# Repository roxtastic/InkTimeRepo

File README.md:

# InkWatch — E-Ink Smartwatch based on nRF52840
Tololoi Ilinca-Roxana, 331CB

A compact, low-power smartwatch built around the Nordic Semiconductor nRF52840 SoC and an e-ink display. The PCB measures 32 x 35 mm with rounded corners to fit a wristwatch enclosure. The design prioritizes ultra-low standby current, BLE connectivity, and an always-on e-paper display that retains its image without any power.

---

## Block Diagram

```
+---------------------+
|     LiPo Battery    |
+----------+----------+
           |
           v
+----------+----------+       +-------------------+
|   Charging IC        |       |   USB Type-C       |
|      TP4054          +<------+   (5V input)       |
+----------+----------+       +-------------------+
           |
           v
+----------+----------+
|   LDO 3.3V           |
|      XC6220          |
+----------+----------+
           |
           v
+----------+-------------------------------------------+
|                      nRF52840                        |
|   Cortex-M4F @ 64 MHz, 1MB Flash, 256KB RAM, BLE 5  |
+---+----------+----------+----------+----------------+
    |          |          |          |
    | SPI      | I2C      | GPIO     | USB
    |          |          |          |
    v          v          v          v
+-------+  +-------+  +-------+  +-----------+
| E-Ink |  | RTC   |  | Btns  |  |  USB CDC  |
| Display  | DS3231|  | x2    |  |  DFU      |
| 200x200  +-------+  +-------+  +-----------+
+-------+  +-------+
           | Haptic|
           | DRV   |
           | 2605L |
           +-------+

+-------+
| Flash |   <-- SPI (shared bus with E-Ink)
| W25Q16|
+-------+
```

---

## Bill of Materials (BOM)

| # | Component | Description | Footprint | Qty | JLC Part | Datasheet |
|---|-----------|-------------|-----------|-----|----------|-----------|
| 1 | nRF52840-QIAA | BLE SoC, Cortex-M4F, 1MB Flash | QFN-73 | 1 | [C190794](https://www.lcsc.com/product-detail/C190794.html) | [Link](https://infocenter.nordicsemi.com/pdf/nRF52840_PS_v1.7.pdf) |
| 2 | GDEW0154M10 | 1.54in E-Ink display, 200x200, SPI | FPC 24-pin | 1 | — | [Link](https://www.good-display.com/product/212.html) |
| 3 | DS3231SN | High-accuracy I2C RTC with TCXO | SOIC-16 | 1 | [C9877](https://www.lcsc.com/product-detail/C9877.html) | [Link](https://datasheets.maximintegrated.com/en/ds/DS3231.pdf) |
| 4 | W25Q16JVSSIQ | 16Mbit SPI NOR Flash | SOIC-8 | 1 | [C131025](https://www.lcsc.com/product-detail/C131025.html) | [Link](https://www.winbond.com/resource-files/w25q16jv%20spi%20revh%2004082019%20plus.pdf) |
| 5 | TP4054 | 500mA single-cell LiPo charger | SOT-23-5 | 1 | [C16581](https://www.lcsc.com/product-detail/C16581.html) | [Link](https://www.lcsc.com/datasheet/lcsc_datasheet_1810192335_TPUNITED-TP4054_C16581.pdf) |
| 6 | XC6220A331MR | 300mA LDO 3.3V regulator | SOT-25 | 1 | [C86534](https://www.lcsc.com/product-detail/C86534.html) | [Link](https://product.torexsemi.com/system/files/series/xc6220.pdf) |
| 7 | DRV2605L | Haptic motor driver, I2C | WSON-10 | 1 | [C167749](https://www.lcsc.com/product-detail/C167749.html) | [Link](https://www.ti.com/lit/ds/symlink/drv2605l.pdf) |
| 8 | PRTR5V0U2X | USB ESD protection, dual-rail | SOT-363 | 1 | [C12333](https://www.lcsc.com/product-detail/C12333.html) | [Link](https://assets.nexperia.com/documents/data-sheet/PRTR5V0U2X.pdf) |
| 9 | USB Type-C connector | USB 2.0 receptacle, mid-mount | SMD | 1 | [C165948](https://www.lcsc.com/product-detail/C165948.html) | — |
| 10 | LiPo 150mAh | 3.7V, 302525 form factor | JST-PH 2-pin | 1 | — | — |
| 11 | Tactile button 3x4mm | Side-press SMD, 4-pin | SMD | 2 | [C318884](https://www.lcsc.com/product-detail/C318884.html) | — |
| 12 | 100nF capacitor 0402 | Decoupling | 0402 | 20 | [C1525](https://www.lcsc.com/product-detail/C1525.html) | — |
| 13 | 10uF capacitor 0805 | Bulk decoupling | 0805 | 5 | [C15850](https://www.lcsc.com/product-detail/C15850.html) | — |
| 14 | 10k resistor 0402 | Pull-ups, voltage divider | 0402 | 15 | [C25744](https://www.lcsc.com/product-detail/C25744.html) | — |
| 15 | 32.768kHz crystal | RTC low-speed oscillator | 3215-2P | 1 | [C32346](https://www.lcsc.com/product-detail/C32346.html) | — |
| 16 | 32MHz crystal | nRF52840 HF oscillator | 3225-4P | 1 | [C9002](https://www.lcsc.com/product-detail/C9002.html) | — |

---

## Hardware Functionality

### Microcontroller — nRF52840

The central component is the Nordic Semiconductor nRF52840, an ARM Cortex-M4F SoC running at up to 64 MHz with 1 MB of internal flash and 256 KB of RAM. It integrates a Bluetooth 5.0 radio, USB 2.0 full-speed device controller, and a rich peripheral set that includes multiple SPI, I2C, UART, PWM, and ADC interfaces. The chip supports a wide supply range from 1.7 V to 5.5 V and multiple deep-sleep modes, making it a natural fit for a battery-powered wearable.

For this board, the nRF52840 runs in its QFN-73 package, clocked by an external 32 MHz crystal for the high-frequency domain and a 32.768 kHz crystal for the low-frequency RTC domain. The internal DC/DC converter is enabled in firmware to reduce dynamic power consumption during active BLE events.

### E-Ink Display

The 1.54-inch 200x200 pixel e-paper panel connects to the nRF52840 over a dedicated 4-wire SPI bus. E-ink technology consumes power only during refresh and holds its image indefinitely at zero standby current — exactly what a watch face display demands. The display interface uses six lines: SPI clock (SCK), MOSI, chip select (CS), data/command (DC), active-low reset (RST), and a BUSY output that the firmware polls before issuing new commands.

Full-screen refresh takes approximately 2 seconds. Panels that support partial refresh can update a region in under 300 ms, which is used for the seconds digit when enabled in firmware.

### Real-Time Clock — DS3231

The DS3231 is a precision I2C RTC with an integrated temperature-compensated crystal oscillator (TCXO), rated at plus or minus 2 ppm. It communicates over the shared I2C bus (SDA, SCL) and provides a square-wave or interrupt output (SQW/INT) on a dedicated GPIO interrupt pin of the nRF52840. Timekeeping continues from the main LiPo through a schottky diode, ensuring the clock does not lose time if the watch is powered off temporarily. The RTC is responsible for waking the nRF52840 from its deep sleep state once per minute to refresh the time display.

### SPI NOR Flash — W25Q16

The 2 MB external flash stores watch face bitmaps, fonts, historical step-count logs, BLE bonding keys, and the OTA firmware update staging area. It shares the SPI bus with the e-ink display but uses its own chip select line. In deep power-down mode the W25Q16 draws under 1 uA, contributing negligibly to the sleep budget.

### Power Management

Charging is performed by the TP4054, a linear single-cell LiPo charger. It accepts 5 V from the USB Type-C connector and charges the 150 mAh cell at a rate set by an external resistor (500 mA maximum). A STAT pin pulls low during charging and is routed to a GPIO pin that drives an indicator LED.

The system 3.3 V rail is generated by the XC6220 LDO, chosen for its 80 mV dropout at 100 mA and a quiescent current of only 1 uA. This is important because the LDO stays active even in deep sleep to power the DS3231 and the nRF52840 retention RAM. The nRF52840 internal DC/DC converter then steps the 3.3 V down further for its core logic.

Battery state of charge is estimated by reading the battery voltage through a resistor divider connected to the nRF52840's SAADC input. The firmware reports this as a BLE Battery Level characteristic and renders a battery icon on the display.

### Haptic Feedback — DRV2605L

The DRV2605L is an I2C haptic motor driver that controls a small ERM (eccentric rotating mass) vibration motor. It integrates a library of 123 licensed waveform effects, so the firmware simply writes a waveform index over I2C and the chip handles the timing and drive current autonomously. An enable GPIO completely removes power from the driver between events, keeping idle current near zero.

### Buttons

Two side-press tactile buttons are connected to GPIO input pins configured with 10 k pull-ups. One button handles navigation (next item / increment) and the other handles confirm or back. Debouncing is implemented in firmware with a 20 ms software timer.

### USB Interface

The USB Type-C connector routes D+ and D- directly to the nRF52840 internal USB PHY. An PRTR5V0U2X ESD protection array is placed immediately beside the connector footprint. In firmware, USB implements both a CDC serial interface (for debug output and log streaming) and a USB DFU class for firmware updates through the MCUboot bootloader.

---

## nRF52840 Pin Assignment

| Pin | Signal | Connected To | Interface | Notes |
|-----|--------|-------------|-----------|-------|
| P0.02 | AIN0 | Battery voltage divider | SAADC | Battery level measurement |
| P0.03 | BTN1 | Tactile button 1 | GPIO IN | 10k pull-up, active low |
| P0.04 | BTN2 | Tactile button 2 | GPIO IN | 10k pull-up, active low |
| P0.06 | UART_TX | Debug UART | UART | Optional, can be repurposed |
| P0.08 | UART_RX | Debug UART | UART | Optional |
| P0.11 | SDA | DS3231, DRV2605L | I2C | Shared I2C bus, 4.7k pull-up |
| P0.12 | SCL | DS3231, DRV2605L | I2C | Shared I2C bus, 4.7k pull-up |
| P0.13 | EINK_SCK | E-Ink display | SPI | Dedicated SPI peripheral |
| P0.14 | EINK_MOSI | E-Ink display | SPI | No MISO needed for display |
| P0.15 | EINK_CS | E-Ink display | SPI CS | Active low |
| P0.16 | EINK_DC | E-Ink display | GPIO OUT | High = data, Low = command |
| P0.17 | EINK_RST | E-Ink display | GPIO OUT | Active low reset |
| P0.18 | EINK_BUSY | E-Ink display | GPIO IN | Polled before each transaction |
| P0.19 | FLASH_SCK | W25Q16 | SPI | Shared SCK with EINK bus |
| P0.20 | FLASH_MOSI | W25Q16 | SPI | Shared MOSI with EINK bus |
| P0.21 | FLASH_MISO | W25Q16 | SPI | Only flash needs MISO |
| P0.22 | FLASH_CS | W25Q16 | SPI CS | Active low, separate from EINK_CS |
| P0.23 | HAPTIC_EN | DRV2605L enable | GPIO OUT | Powers down driver when low |
| P0.24 | RTC_INT | DS3231 SQW/INT | GPIO IN | Wake from System OFF sleep |
| P0.25 | CHG_STAT | TP4054 STAT | GPIO IN | Charging indicator logic |
| P1.09 | LED | Status LED | GPIO OUT | Optional charge/notification LED |
| D+ / D- | USB_DP / USB_DM | USB Type-C via ESD | USB 2.0 | Full-speed USB PHY |
| VDD | 3.3V | XC6220 output | Power | Main supply |
| VDDUSB | 3.3V | Shared rail | Power | USB PHY supply |
| GND | GND | Copper pour | — | Both layers, stitched |

The SPI bus serving the e-ink display and the NOR flash is physically shared (same SCK, MOSI, MISO traces) but each peripheral has an independent chip select driven by the nRF52840, preventing simultaneous transactions.

---

## Power Budget Estimate

| Operating State | Current | Duration per Minute | Charge per Minute |
|----------------|---------|--------------------|--------------------|
| Deep sleep (RTC alive, nRF off) | ~3 uA | 57 s | ~171 uA·s |
| CPU active (no radio) | ~2 mA | 0.5 s | ~1 mA·s |
| E-Ink full refresh | ~15 mA | 2 s | ~30 mA·s |
| BLE advertisement burst | ~5 mA | 0.5 s | ~2.5 mA·s |
| Average per minute | ~3.6 uA avg | — | ~34.7 uA·s |

With a 150 mAh (540 000 uA·s) cell, estimated battery life in time-display-only mode with one BLE sync per minute is approximately 35 to 40 days. Enabling continuous notification mirroring (BLE connected, scan interval 100 ms) reduces this to roughly 7 to 10 days.

---

## PCB Design Notes

The board is a 2-layer design at 32 x 35 mm with 4 mm corner radius, sized to fit a standard 34 mm watch case inner cavity. Design decisions:

- The nRF52840 sits near the center of the board to keep trace lengths short to all SPI and I2C peripherals.
- The 2.4 GHz antenna keep-out zone occupies the upper edge of the board. Both copper layers are cleared in this area and the zone extends 3 mm beyond the board edge as a trace antenna. No components are placed under the antenna.
- Every VDD supply pin on the nRF52840 has a 100 nF decoupling capacitor within 0.5 mm, with vias to the ground plane directly beside the capacitor pad.
- The TP4054 and XC6220 are grouped near the USB connector to minimize the length of high-current charging traces.
- The e-ink FPC connector is on the top edge of the PCB so the display can fold flat over the board.
- The LiPo cell mounts to the back of the case and connects through a JST-PH 2-pin connector on the bottom edge.

## Firmware Overview

The firmware targets the Zephyr RTOS with the nRF Connect SDK. Key components:

- **Display driver** — custom SPI driver implementing full and partial refresh sequences for the e-paper panel, with a framebuffer held in nRF52840 RAM
- **BLE stack** — Zephyr Bluetooth stack exposing a Current Time Service (CTS) profile, Battery Level Service, and a proprietary notification characteristic
- **RTC synchronization** — on each BLE connection, the companion app writes the current Unix timestamp to the CTS characteristic; between connections the DS3231 maintains time independently
- **Power management** — an application-level sleep manager issues `pm_state_force(PM_STATE_SOFT_OFF)` between minute ticks; the DS3231 SQW interrupt on P0.24 triggers a full reset/wakeup via the nRF52840 GPIO sense mechanism
- **MCUboot + USB DFU** — dual-slot bootloader supporting firmware updates over USB DFU without a hardware programmer

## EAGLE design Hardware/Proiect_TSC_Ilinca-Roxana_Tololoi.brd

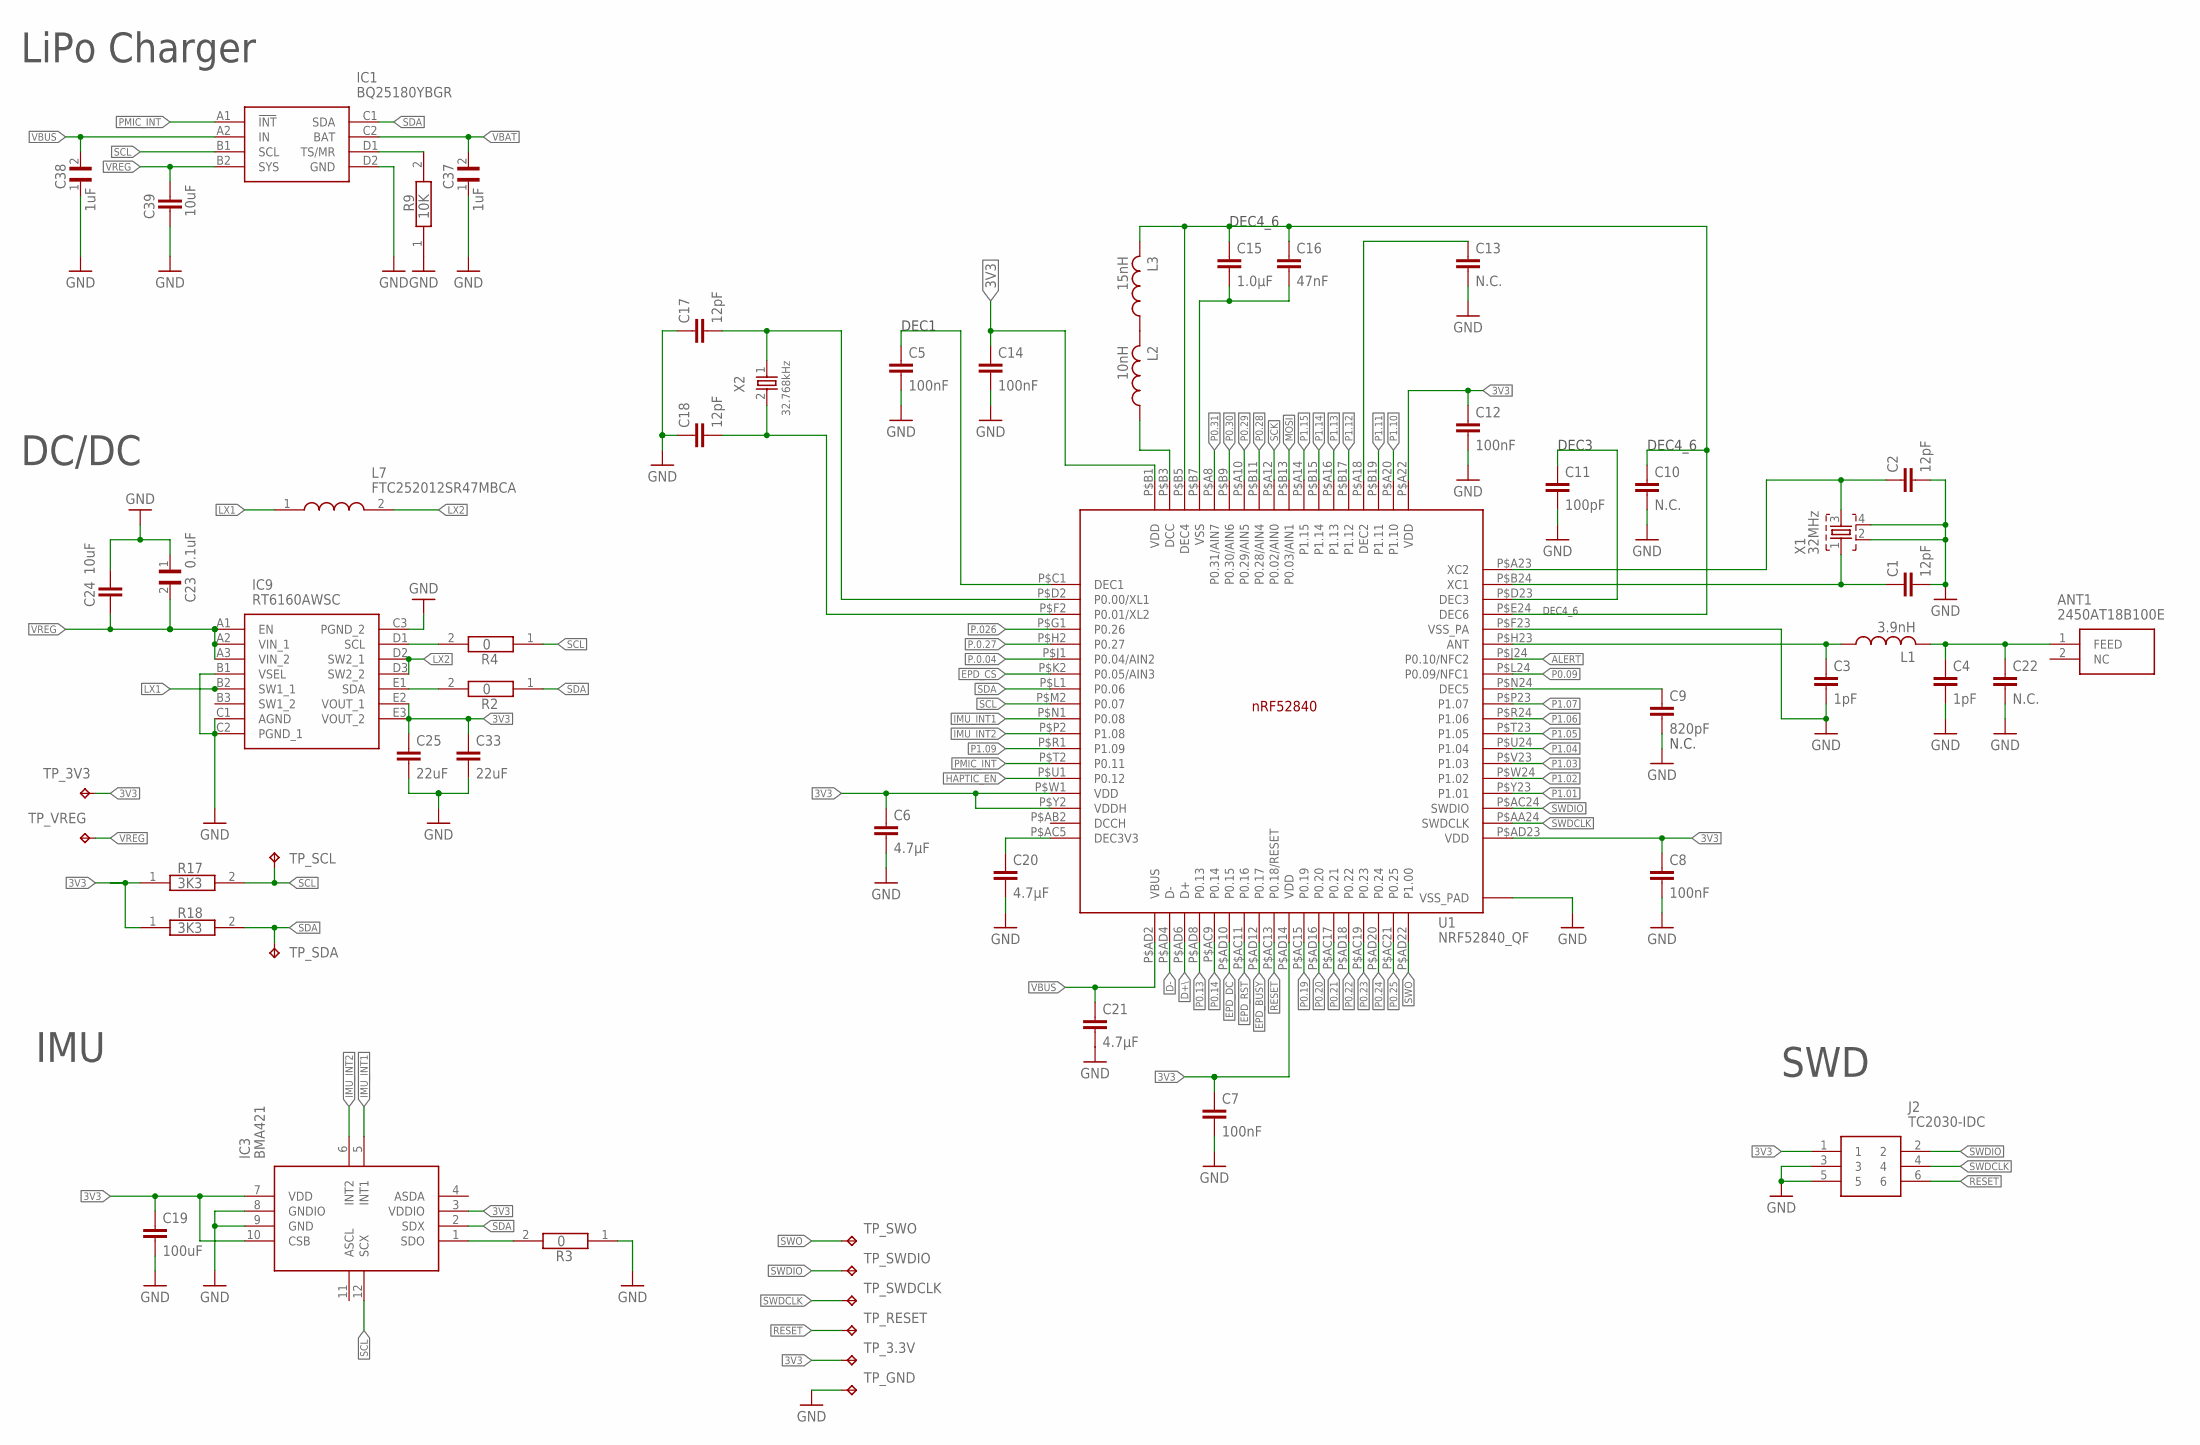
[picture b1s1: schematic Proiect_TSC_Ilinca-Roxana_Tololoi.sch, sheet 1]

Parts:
ANT1: 2450AT18B100E; 2450AT18B100E_ANTC3216X140N
C1, C2, C17, C18: 12pF; PERFECT_0402_0402
C3, C4: 1pF; PERFECT_0402_0402
C5, C7, C8, C12, C14: 100nF; PERFECT_0402_0402
C6, C20, C21: 4.7μF; PERFECT_0402_0402
C9: 820pF; PERFECT_0402_0402
C10, C13, C22: N.C.; PERFECT_0402_0402
C11: 100pF; PERFECT_0402_0402
C15: 1.0μF; PERFECT_0402_0402
C16: 47nF; PERFECT_0402_0402
C19: 100uF; PERFECT_0402_0402
C23: 0.1uF; GRM011R60J152KE01L_2_CAPC0201X13N
C24, C39: 10uF; PERFECT_0402_0402
C25, C33: 22uF; PERFECT_0402_0402
C37, C38: 1uF; GRM011R60J152KE01L_2_CAPC0201X13N
IC1: BQ25180YBGR; BQ25180YBGR_BGA8C40P2X4_100X155X50
IC3: BMA421; BMA423_BMA423
IC9: RT6160AWSC; RT6160AWSC_BGA15C40P3X5_140X230X60
J2: TC2030-IDC; TC2030-IDC_TC2030IDC
L1: 3.9nH; NORDIC_NRF_2_RESC0402_L
L2: 10nH; NORDIC_NRF_2_RESC0402_L
L3: 15nH; NORDIC_NRF_2_RESC0402_L
L7: FTC252012SR47MBCA; MLP2016SR47MT0S1_INDC2016X100N
R2, R3, R4: 0; ERA-1AEB3401C_0201
R9: 10K; ERA-1AEB3401C_0201
R17, R18: 3K3; ERA-1AEB3401C_0201
TP_3.3V, TP_3V3: HECTOR_WATCH_1_TPTP20R; HECTOR_WATCH_1_TP20R
TP_GND: HECTOR_WATCH_1_TPTP20R; HECTOR_WATCH_1_TP20R
TP_RESET: HECTOR_WATCH_1_TPTP20R; HECTOR_WATCH_1_TP20R
TP_SCL: HECTOR_WATCH_1_TPTP20R; HECTOR_WATCH_1_TP20R
TP_SDA: HECTOR_WATCH_1_TPTP20R; HECTOR_WATCH_1_TP20R
TP_SWDCLK: HECTOR_WATCH_1_TPTP20R; HECTOR_WATCH_1_TP20R
TP_SWDIO: HECTOR_WATCH_1_TPTP20R; HECTOR_WATCH_1_TP20R
TP_SWO: HECTOR_WATCH_1_TPTP20R; HECTOR_WATCH_1_TP20R
TP_VREG: HECTOR_WATCH_1_TPTP20R; HECTOR_WATCH_1_TP20R
U1: NRF52840_QF; NORDIC_NRF_4_AQFN50P700X700X85_HS-74N
X1: 32MHz; NORDIC_NRF_BT-XTAL_2016_N
X2: 32.768kHz; NORDIC_NRF_1_XTAL_3215_N

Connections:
3V3: C6.1, C7.1, C8.1, C12.1, C14.1, C19.1, C25.1, C33.1, IC3.3 (VDDIO), IC3.7 (VDD), IC3.10 (CSB), IC9.E2 (VOUT_1), IC9.E3 (VOUT_2), J2.1, R17.1, R18.1, TP_3.3V.TP, TP_3V3.TP, U1.P$A22 (VDD), U1.P$AD14 (VDD), U1.P$AD23 (VDD), U1.P$B1 (VDD), U1.P$W1 (VDD), U1.P$Y2 (VDDH); also elsewhere on the board
ALERT: U1.P$J24 (P0.10/NFC2); also elsewhere on the board
D+\: U1.P$AD6 (D+)
D-: U1.P$AD4 (D-); also elsewhere on the board
EPD_BUSY: U1.P$AD12 (P0.17); also elsewhere on the board
EPD_CS: U1.P$K2 (P0.05/AIN3); also elsewhere on the board
EPD_DC: U1.P$AD10 (P0.15); also elsewhere on the board
EPD_RST: U1.P$AC11 (P0.16); also elsewhere on the board
GND: C1.2, C2.2, C3.2, C4.2, C5.2, C6.2, C7.2, C8.2, C9.2, C10.2, C11.2, C12.2, C13.2, C14.2, C17.1, C18.1, C19.2, C20.2, C21.2, C22.2, C23.1, C24.1, C25.2, C33.2, C37.1, C38.1, C39.2, IC1.D2 (GND), IC3.8 (GNDIO), IC3.9 (GND), IC9.B1 (VSEL), IC9.C1 (AGND), IC9.C2 (PGND_1), IC9.C3 (PGND_2), J2.3, J2.5, R3.1, R9.1, TP_GND.TP, U1.P$74 (VSS_PAD), U1.P$75 (VSS_PAD), U1.P$76 (VSS_PAD), U1.P$77 (VSS_PAD), U1.P$78 (VSS_PAD), U1.P$79 (VSS_PAD), U1.P$80 (VSS_PAD), U1.P$81 (VSS_PAD), U1.P$82 (VSS_PAD), U1.P$83 (VSS_PAD), U1.P$84 (VSS_PAD), U1.P$85 (VSS_PAD), U1.P$86 (VSS_PAD), U1.P$87 (VSS_PAD), U1.P$88 (VSS_PAD), U1.P$89 (VSS_PAD), U1.P$90 (VSS_PAD), U1.P$F23 (VSS_PA), X1.2, X1.4; also elsewhere on the board
HAPTIC_EN: U1.P$U1 (P0.12); also elsewhere on the board
IMU_INT1: IC3.5 (INT1), U1.P$N1 (P0.08)
IMU_INT2: IC3.6 (INT2), U1.P$P2 (P1.08)
LX1: IC9.B2 (SW1_1), L7.1
LX2: IC9.D2 (SW2_1), IC9.D3 (SW2_2), L7.2
MOSI: U1.P$B13 (P0.03/AIN1); also elsewhere on the board
unnamed: IC1.D1 (TS/MR), R9.2
unnamed: IC9.D1 (SCL), R4.2
unnamed: IC9.E1 (SDA), R2.2
unnamed: C18.2, U1.P$F2 (P0.01/XL2), X2.2
unnamed: C20.1, U1.P$AC5 (DEC3V3)
unnamed: IC3.1 (SDO), R3.2
unnamed: C17.2, U1.P$D2 (P0.00/XL1), X2.1
unnamed: L2.2, L3.1
unnamed: C2.1, U1.P$A23 (XC2), X1.3
unnamed: C1.1, U1.P$B24 (XC1), X1.1
unnamed: C5.1, U1.P$C1 (DEC1)
unnamed: L2.1, U1.P$B3 (DCC)
unnamed: ANT1.1 (FEED), C4.1, C22.1, L1.2
unnamed: C15.2, C16.2, U1.P$B7 (VSS)
unnamed: C9.1, U1.P$N24 (DEC5)
unnamed: C3.1, L1.1, U1.P$H23 (ANT)
unnamed: C10.1, C15.1, C16.1, L3.2, U1.P$B5 (DEC4), U1.P$E24 (DEC6)
unnamed: C11.1, U1.P$D23 (DEC3)
unnamed: C13.1, U1.P$A18 (DEC2)
P0.09: U1.P$L24 (P0.09/NFC1)
P0.13: U1.P$AD8 (P0.13); also elsewhere on the board
P0.14: U1.P$AC9 (P0.14); also elsewhere on the board
P0.19: U1.P$AC15 (P0.19)
P0.20: U1.P$AD16 (P0.20)
P0.21: U1.P$AC17 (P0.21)
P0.22: U1.P$AD18 (P0.22)
P0.23: U1.P$AC19 (P0.23)
P0.24: U1.P$AD20 (P0.24)
P0.25: U1.P$AC21 (P0.25)
P0.28: U1.P$B11 (P0.28/AIN4)
P0.29: U1.P$A10 (P0.29/AIN5)
P0.30: U1.P$B9 (P0.30/AIN6)
P0.31: U1.P$A8 (P0.31/AIN7)
P1.01: U1.P$Y23 (P1.01); also elsewhere on the board
P1.02: U1.P$W24 (P1.02); also elsewhere on the board
P1.03: U1.P$V23 (P1.03)
P1.04: U1.P$U24 (P1.04)
P1.05: U1.P$T23 (P1.05)
P1.06: U1.P$R24 (P1.06)
P1.07: U1.P$P23 (P1.07)
P1.09: U1.P$R1 (P1.09)
P1.10: U1.P$A20 (P1.10)
P1.11: U1.P$B19 (P1.11)
P1.12: U1.P$B17 (P1.12)
P1.13: U1.P$A16 (P1.13)
P1.14: U1.P$B15 (P1.14)
P1.15: U1.P$A14 (P1.15)
P.0.04: U1.P$J1 (P0.04/AIN2)
P.0.27: U1.P$H2 (P0.27)
P.026: U1.P$G1 (P0.26)
PMIC_INT: IC1.A1 (!INT), U1.P$T2 (P0.11)
RESET: J2.6, TP_RESET.TP, U1.P$AC13 (P0.18/RESET)
SCK: U1.P$A12 (P0.02/AIN0); also elsewhere on the board
SCL: IC1.B1 (SCL), IC3.12 (SCX), R4.1, R17.2, TP_SCL.TP, U1.P$M2 (P0.07); also elsewhere on the board
SDA: IC1.C1 (SDA), IC3.2 (SDX), R2.1, R18.2, TP_SDA.TP, U1.P$L1 (P0.06); also elsewhere on the board
SWDCLK: J2.4, TP_SWDCLK.TP, U1.P$AA24 (SWDCLK)
SWDIO: J2.2, TP_SWDIO.TP, U1.P$AC24 (SWDIO)
SWO: TP_SWO.TP, U1.P$AD22 (P1.00)
VBAT: C37.2, IC1.C2 (BAT); also elsewhere on the board
VBUS: C21.1, C38.2, IC1.A2 (IN), U1.P$AD2 (VBUS); also elsewhere on the board
VREG: C23.2, C24.2, C39.1, IC1.B2 (SYS), IC9.A1 (EN), IC9.A2 (VIN_1), IC9.A3 (VIN_2), TP_VREG.TP

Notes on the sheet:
LiPo Charger
DC/DC
IMU
SWD
DEC3
N.C.
DEC4_6
DEC1

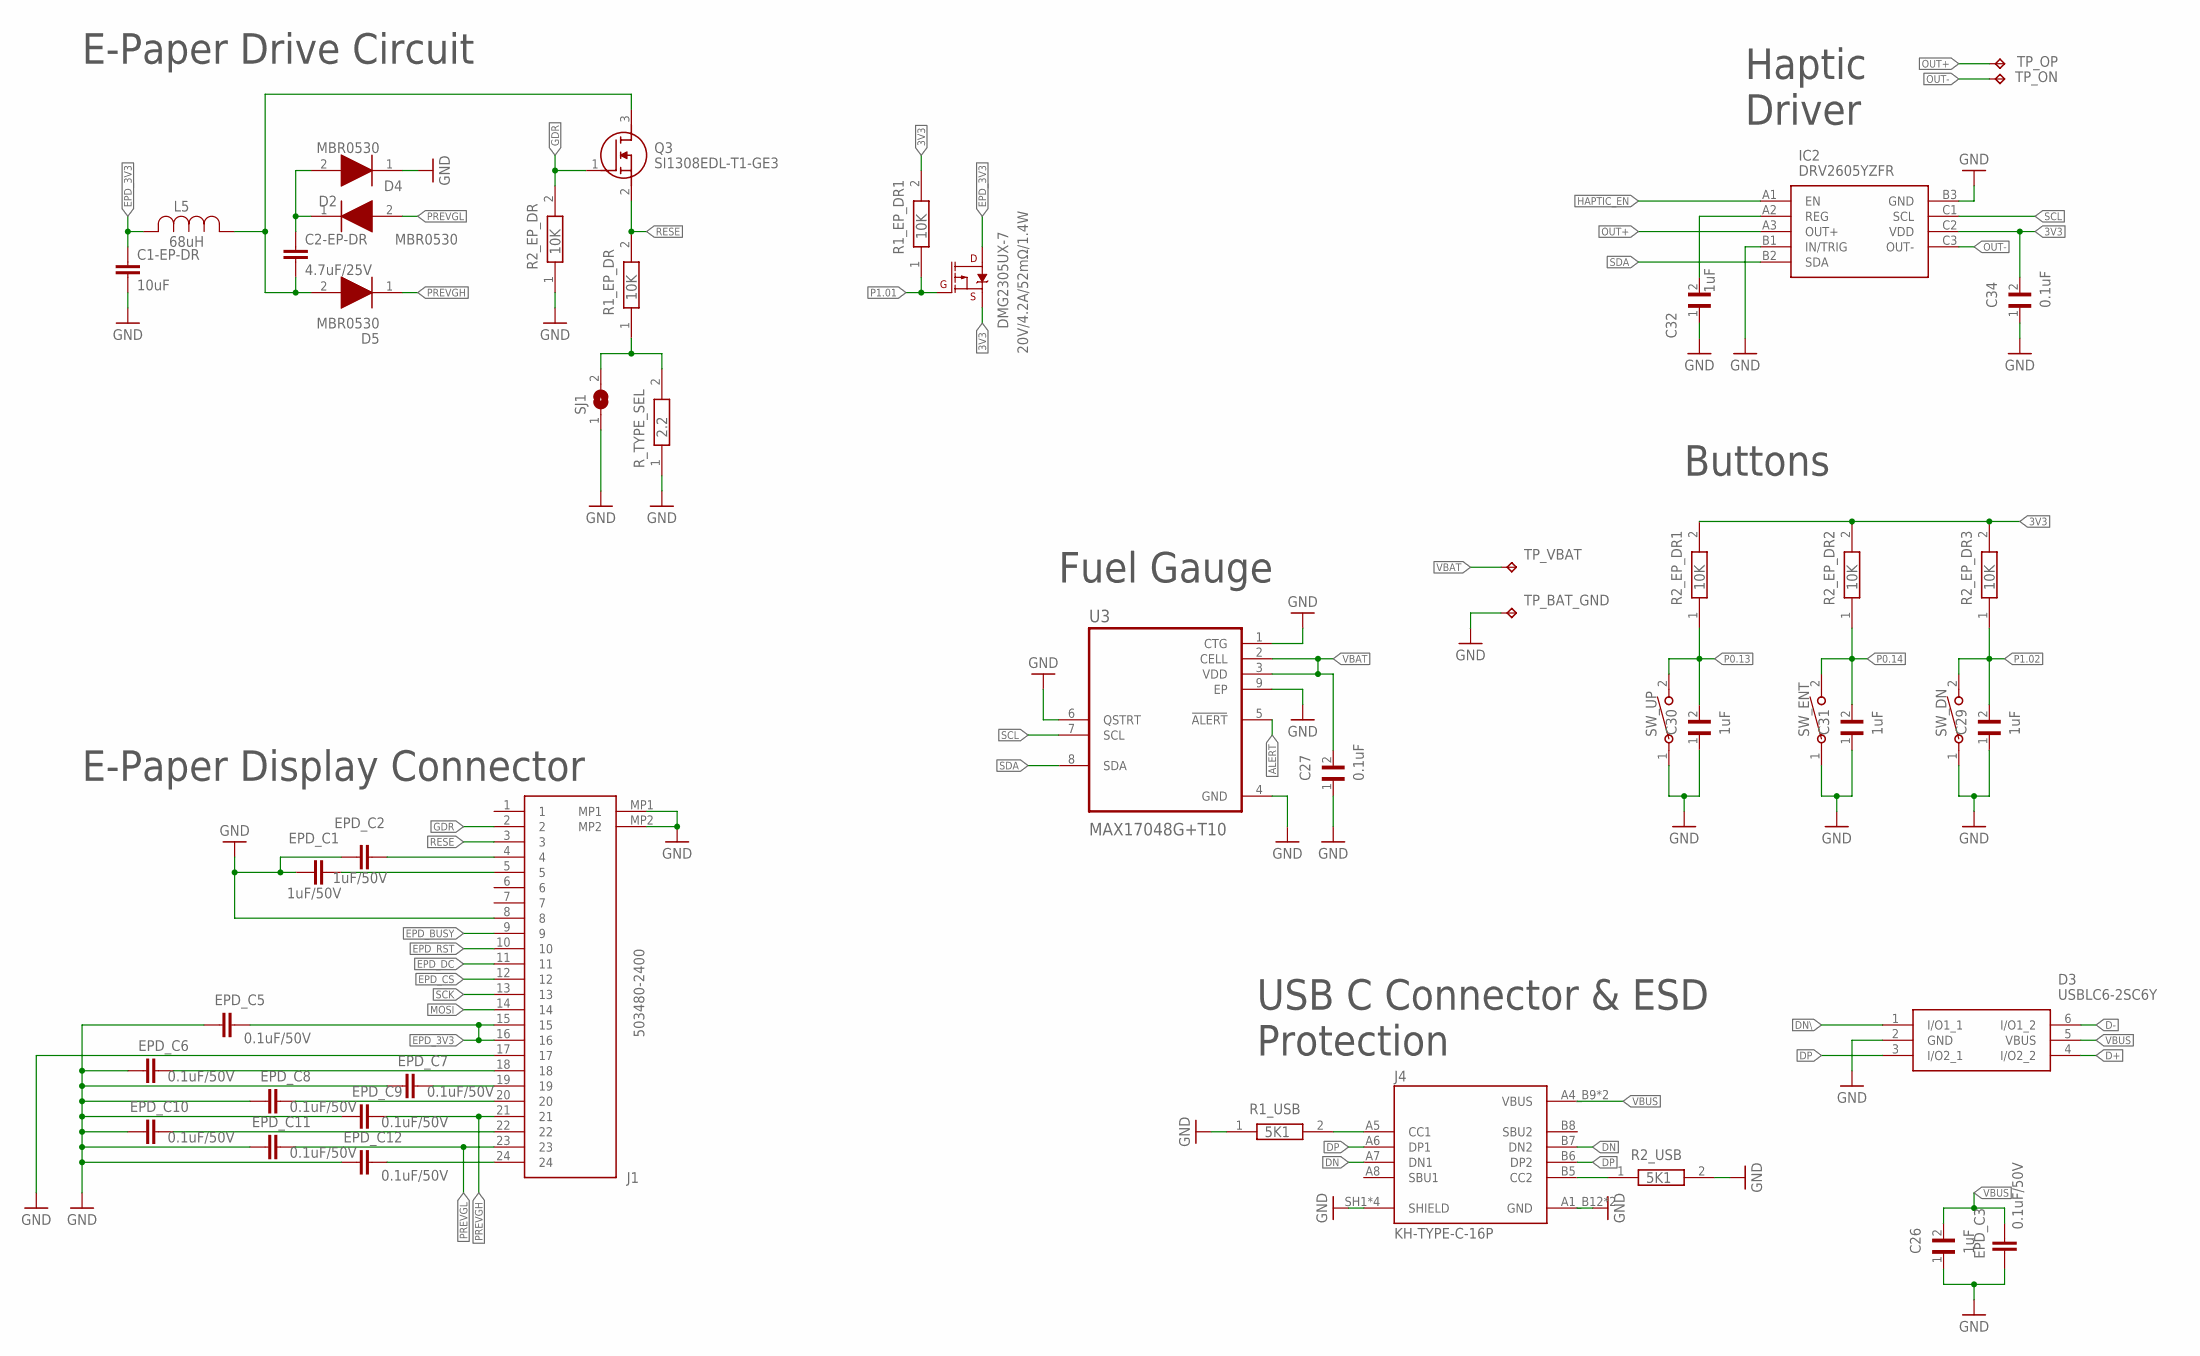
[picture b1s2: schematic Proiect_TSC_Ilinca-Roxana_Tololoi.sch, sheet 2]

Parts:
C1-EP-DR: 10uF; PERFECT_0402_0402
C2-EP-DR: 4.7uF/25V; PERFECT_0402_0402
C26, C29, C30, C31, C32: 1uF; GRM011R60J152KE01L_1_0201
C27, C34: 0.1uF; GRM011R60J152KE01L_1_0201
D2, D4, D5: MBR0530; ESP32_C6_LIBRARY_5_SOD3716X135N
D3: USBLC6-2SC6Y; ESP32_C6_LIBRARY_3_SOT95P280X145-6N
DMG2305UX-7: 20V/4.2A/52mΩ/1.4W; ESP32_C6_LIBRARY_4_ESP32_C6_LIBRARY_4_ESP32_C6_LIBRARY_4_ES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
EPD_C1, EPD_C2: 1uF/50V; PERFECT_0402_0402
EPD_C3, EPD_C5, EPD_C6, EPD_C7, EPD_C8, EPD_C9, EPD_C10, EPD_C11, EPD_C12: 0.1uF/50V; PERFECT_0402_0402
IC2: DRV2605YZFR; DRV2605YZFR_BGA9C50P3X3_144X144X62
J1: 503480-2400; 503480-2400_5034802400
J4: KH-TYPE-C-16P; KH-TYPE-C-16P_KINGHELM_KH-TYPE-C-16P
L5: 68uH; ESP32_C6_LIBRARY_2_IND_4828-WE-TPC_WRE
Q3: SI1308EDL-T1-GE3; ESP32_C6_LIBRARY_6_SOT65P210X110-3N
R1_EP_DR, R1_EP_DR1, R2_EP_DR, R2_EP_DR1, R2_EP_DR2, R2_EP_DR3: 10K; ERA-1AEB3401C_0201
R1_USB, R2_USB: 5K1; ERA-1AEB3401C_0201
R_TYPE_SEL: 2.2; ERA-1AEB3401C_0201
SJ1: ESP32_C6_LIBRARY_7_JUMPER_SJ
SW_DN: 2025-10-22_07-23-44_LIBRARY_EVP-AKE31ASW_EVP-AKE3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; 2025-10-22_07-23-44_LIBRARY_SW_EVP-AKE31A_PAN
SW_ENT: 2025-10-22_07-23-44_LIBRARY_EVP-AKE31ASW_EVP-AKE3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; 2025-10-22_07-23-44_LIBRARY_SW_EVP-AKE31A_PAN
SW_UP: 2025-10-22_07-23-44_LIBRARY_EVP-AKE31ASW_EVP-AKE3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; 2025-10-22_07-23-44_LIBRARY_SW_EVP-AKE31A_PAN
TP_BAT_GND: HECTOR_WATCH_1_TPTP20R; HECTOR_WATCH_1_TP20R
TP_ON: HECTOR_WATCH_1_TPTP20R; HECTOR_WATCH_1_TP20R
TP_OP: HECTOR_WATCH_1_TPTP20R; HECTOR_WATCH_1_TP20R
TP_VBAT: HECTOR_WATCH_1_TPTP20R; HECTOR_WATCH_1_TP20R
U3: MAX17048G+T10; ESP32_C6_LIBRARY_SON50P200X200X80-9N

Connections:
3V3: C34.2, DMG2305UX-7.2 (S), IC2.C2 (VDD), R1_EP_DR1.2, R2_EP_DR1.2, R2_EP_DR2.2, R2_EP_DR3.2; also elsewhere on the board
ALERT: U3.5 (!ALERT); also elsewhere on the board
D+: D3.4 (I/O2_2)
D-: D3.6 (I/O1_2); also elsewhere on the board
DN: J4.A7 (DN1), J4.B7 (DN2)
DN\: D3.1 (I/O1_1)
DP: D3.3 (I/O2_1), J4.A6 (DP1), J4.B6 (DP2)
EPD_3V3: C1-EP-DR.1, DMG2305UX-7.3 (D), EPD_C5.2, J1.15, J1.16, L5.2
EPD_BUSY: J1.9; also elsewhere on the board
EPD_CS: J1.12; also elsewhere on the board
EPD_DC: J1.11; also elsewhere on the board
EPD_RST: J1.10; also elsewhere on the board
GDR: J1.2, Q3.1 (G), R2_EP_DR.2
GND: C1-EP-DR.2, C26.1, C27.1, C29.1, C30.1, C31.1, C32.1, C34.1, D3.2 (GND), D4.1 (K), EPD_C1.1, EPD_C2.1, EPD_C3.1, EPD_C5.1, EPD_C6.1, EPD_C7.1, EPD_C8.1, EPD_C9.1, EPD_C10.1, EPD_C11.1, EPD_C12.1, IC2.B1 (IN/TRIG), IC2.B3 (GND), J1.8, J1.17, J1.MP1, J1.MP2, J4.A1_B12 (GND), J4.A12_B1 (GND), J4.SH1 (SHIELD), J4.SH2 (SHIELD), J4.SH3 (SHIELD), J4.SH4 (SHIELD), R1_USB.1, R2_EP_DR.1, R2_USB.2, R_TYPE_SEL.1, SJ1.1, SW_DN.1, SW_ENT.1, SW_UP.1, TP_BAT_GND.TP, U3.1 (CTG), U3.4 (GND), U3.6 (QSTRT), U3.9 (EP); also elsewhere on the board
HAPTIC_EN: IC2.A1 (EN); also elsewhere on the board
MOSI: J1.14; also elsewhere on the board
unnamed: C2-EP-DR.2, D5.2 (A), L5.1, Q3.3 (D)
unnamed: C2-EP-DR.1, D2.1 (K), D4.2 (A)
unnamed: EPD_C1.2, J1.5
unnamed: R1_EP_DR.1, R_TYPE_SEL.2, SJ1.2
unnamed: C32.2, IC2.A2 (REG)
unnamed: EPD_C6.2, J1.18
unnamed: EPD_C2.2, J1.4
unnamed: EPD_C7.2, J1.19
unnamed: EPD_C8.2, J1.20
unnamed: EPD_C10.2, J1.22
unnamed: EPD_C11.2, J1.23
unnamed: EPD_C12.2, J1.24
unnamed: J4.A5 (CC1), R1_USB.2
unnamed: J4.B5 (CC2), R2_USB.1
OUT+: IC2.A3 (OUT+), TP_OP.TP
OUT-: IC2.C3 (OUT-), TP_ON.TP
P0.13: C30.2, R2_EP_DR1.1, SW_UP.2; also elsewhere on the board
P0.14: C31.2, R2_EP_DR2.1, SW_ENT.2; also elsewhere on the board
P1.01: DMG2305UX-7.1 (G), R1_EP_DR1.1; also elsewhere on the board
P1.02: C29.2, R2_EP_DR3.1, SW_DN.2; also elsewhere on the board
PREVGH: D5.1 (K), EPD_C9.2, J1.21
PREVGL: D2.2 (A)
RESE: J1.3, Q3.2 (S), R1_EP_DR.2
SCK: J1.13; also elsewhere on the board
SCL: IC2.C1 (SCL), U3.7 (SCL); also elsewhere on the board
SDA: IC2.B2 (SDA), U3.8 (SDA); also elsewhere on the board
VBAT: C27.2, TP_VBAT.TP, U3.2 (CELL), U3.3 (VDD); also elsewhere on the board
VBUS: C26.2, D3.5 (VBUS), EPD_C3.2, J4.A4_B9 (VBUS), J4.A9_B4 (VBUS); also elsewhere on the board

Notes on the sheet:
E-Paper Drive Circuit
Haptic Driver
E-Paper Display Connector
Fuel Gauge
Buttons
USB C Connector & ESD Protection

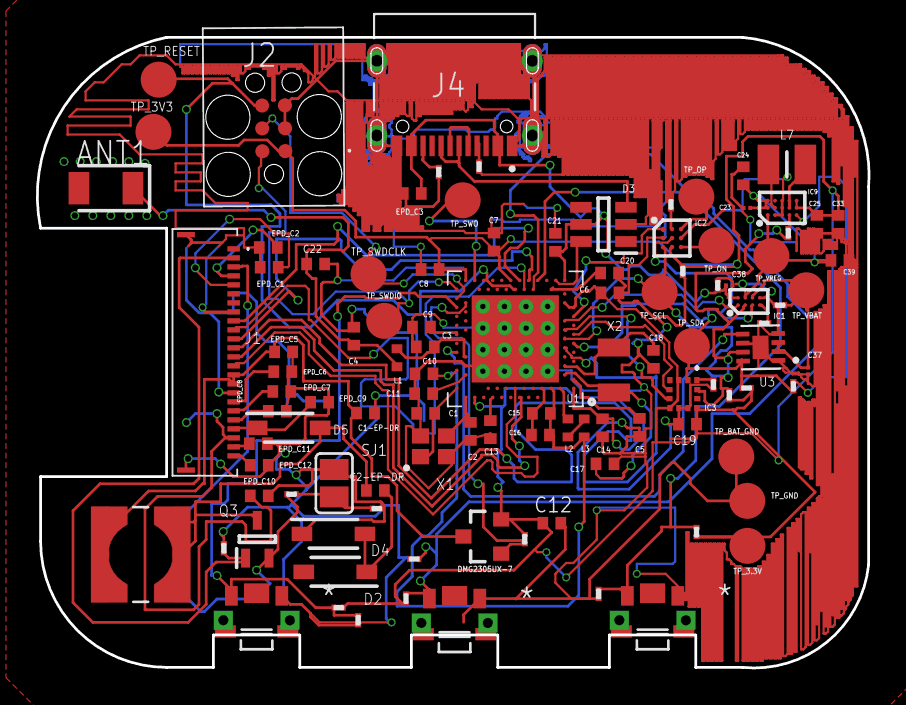
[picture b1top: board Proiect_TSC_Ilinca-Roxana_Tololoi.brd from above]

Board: 4 copper layers, 46.2 x 35.0 mm, 105 parts (0 on the bottom side), 70 nets.

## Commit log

2026-04-11 Hardware
2026-04-20 Updated project after review
2026-05-02 Final version of PCB

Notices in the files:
parts and their libraries:
COPYRIGHT: Copyright (C) 2024 Ultra Librarian. All rights reserved.
COPYRIGHT: Copyright (C) 2025 Ultra Librarian. All rights reserved.
